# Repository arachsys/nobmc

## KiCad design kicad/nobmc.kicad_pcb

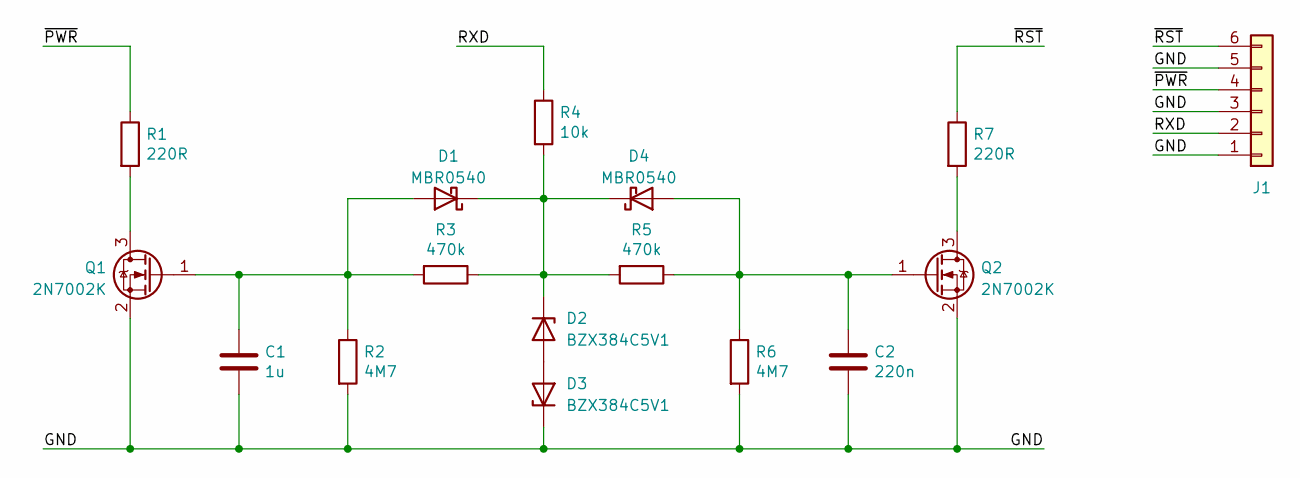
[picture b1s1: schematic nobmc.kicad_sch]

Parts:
C1: 1u; C_0805_2012Metric
C2: 220n; C_0805_2012Metric
D1, D4: MBR0540; D_SOD-123
D2, D3: BZX384C5V1; D_SOD-323
J1: Conn_01x06; PinHeader_1x06_P2.54mm_Horizontal
Q1, Q2: 2N7002K; SOT-23
R1, R7: 220R; R_0603_1608Metric
R2, R6: 4M7; R_0603_1608Metric
R3, R5: 470k; R_0603_1608Metric
R4: 10k; R_0603_1608Metric

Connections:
/GND: C1.2, C2.2, D3.1 (K), J1.1, J1.3, J1.5, Q1.2 (S), Q2.2 (S), R2.2, R6.2
/RXD: J1.2, R4.1
/~PWR: J1.4, R1.1
/~RST: J1.6, R7.1
unnamed: C1.1, D1.2 (A), Q1.1 (G), R2.1, R3.2
unnamed: D1.1 (K), D2.1 (K), D4.1 (K), R3.1, R4.2, R5.2
unnamed: D2.2 (A), D3.2 (A)
unnamed: C2.1, D4.2 (A), Q2.1 (G), R5.1, R6.1
unnamed: Q1.3 (D), R1.2
unnamed: Q2.3 (D), R7.2

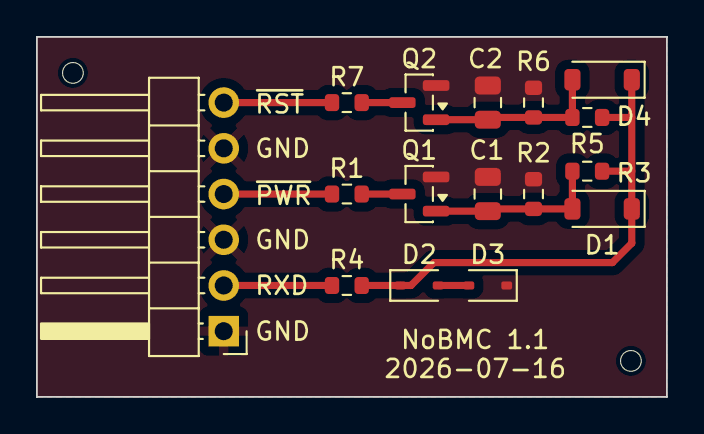
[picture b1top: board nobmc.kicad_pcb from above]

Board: 2 copper layers, 35.0 x 20.0 mm, 18 parts (0 on the bottom side), 10 nets.

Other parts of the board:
HOLE: ToolingHole_1.152mm
HOLE#2: ToolingHole_1.152mm

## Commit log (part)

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2023-02-26 Import initial version
2023-02-26 Add COPYING
